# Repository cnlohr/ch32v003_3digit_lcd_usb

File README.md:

# ch32v003_3digit_lcd_usb

USB, Touch and Driver for 3-digit 7-segment TN LCDs on CH32V003

[Youtube Video](https://www.youtube.com/watch?v=KNDRUWlsu0k)

Using a ch32v003, a 10 cent microcontroller, without USB, Touch or LCD Driving capaibilities to do all three at the same time.

## Design

The design uses the reference rv003usb pinout, simply run the ch32v003 at 3.3v with an LDO and connect it up to the USB paddle card.

Conveniently the paddle card uses the same pinout as a normal USB Connector.

The overall board uses the inside part of a USB Type C connector, but as part of the PCB, so there are the following two recommendations:

1. Your PCB should be 0.6mm thick.
2. Your PCB sohuld use ENIG finish instead of HASL, as it is possible a HASL finish could damage USB-C cables.

The ch32v003 needs no preprogramming, only access to the GND/SWIO/5V pins to flash the bootloader on.

To use this design, your LCD must be a 3V LCD and should match the following specification:

## Software

To flash on the software, you should:

 * Optionally, install the rv003usb bootloader.

Then, from either external programmer or bootloader,

 * In your desired firmware folder type `make option_write`
 * Flash with `make flash`

Appropriate firmware can be found in the firmware/ folders.  When cloning this repo, be sure to clone recursively, i.e.

```
git clone https://github.com/cnlohr/ch32v003_3digit_lcd_usb --recursive
```

or if you, forgot, cd into the folder and run:
```
git submodule update --init --recursive
```

## Touch Sensing

To perform touch sensing, we drive the line low, then, in concert with starting the ADC sample (and making sure the ADC setup/sample is aligned in time to Fcpu/2) we apply a pull-up resistor to all the ports on the LCD.

This causes a measurement to be made as the voltage on the pins common to the whole LCD is rising and this gives us our measurement.

## Waveforms

For basic LCD output, you can use a fairly simple waveform that has 10 stages.

 * Stages 0..3 = Specific COM pins are driven LOW in succession, while any segments to light are turned HIGH.
 * Stage 4 = Free time, make sure there is no voltage differential.  This also helps control contrast.
 * Stage 5..8 = Specific COM pins are driven HIGH in succession, while any segments to light are turned LOW.
 * Stage 9 = The other half of the free time for contrast.

You can see how enabling USB wrecks things up, because with USB going, it can't regulate the SEG pins to 1/2 VCC.

For touch, the output is repeatedly released from a low voltage with an internal pullup while simultaneously measuring the voltage with an ADC to obtain the touch amount.

Which looks great until USB sails its boat into it.

## Resources

 * Applicaiton Note: [NXP AN3129](https://www.nxp.com/docs/en/application-note/AN3219.pdf)
 * [ch32v003fun](https://github.com/cnlohr/ch32v003fun)
 * [rv003usb](https://github.com/cnlohr/ch32v003fun)

Search Aliexpress for "TN LCD Segment" to find these little bad boys.

## License

All code and designs may by licensed freely under the MIT/x11 License.

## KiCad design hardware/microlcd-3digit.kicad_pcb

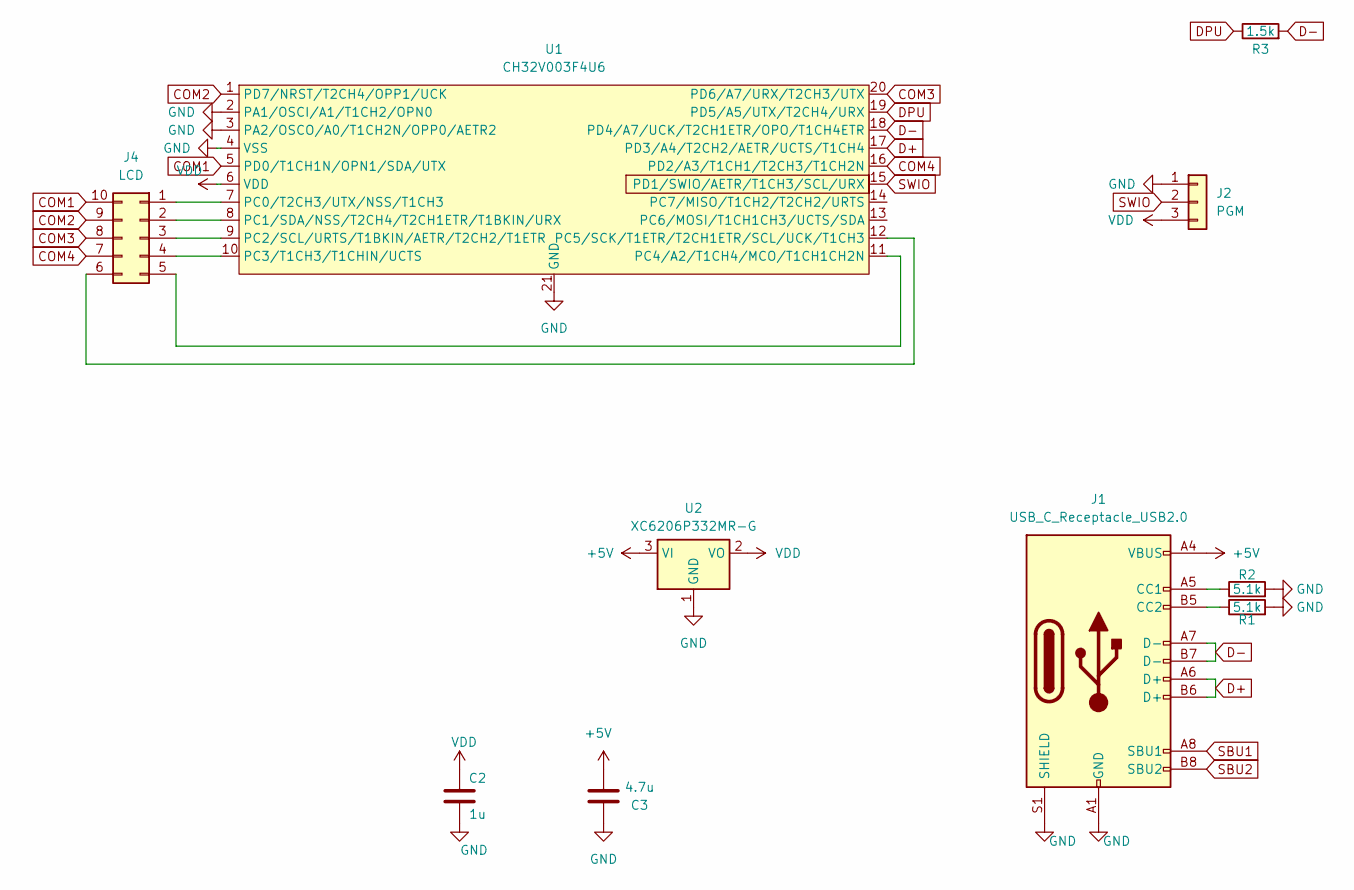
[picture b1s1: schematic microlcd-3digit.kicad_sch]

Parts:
C2: 1u; R_0402_1005Metric; LCSC C52923
C3: 4.7u; R_0402_1005Metric; LCSC C23733
J1: USB_C_Receptacle_USB2.0; USB_C_PADDLE
J2: PGM; PinHeader_1x03_P2.54mm_Vertical
J4: LCD; TINY_LCD_3_DIGIT
R1, R2: 5.1k; R_0402_1005Metric; LCSC C25905
R3: 1.5k; R_0402_1005Metric; LCSC C25867
U1: CH32V003F4U6; QFN-20-1EP_3x3mm_P0.4mm_EP1.65x1.65mm; LCSC C5299908
U2: XC6206P332MR-G; SOT-23; LCSC C5446

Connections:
+5V: C3.2, J1.A4 (VBUS), J1.A9 (VBUS), J1.B4 (VBUS), J1.B9 (VBUS), U2.3 (VI)
COM1: J4.7, U1.16 (PD2/A3/T1CH1/T2CH3/T1CH2N)
COM2: J4.8, U1.20 (PD6/A7/URX/T2CH3/UTX)
COM3: J4.9, U1.1 (PD7/NRST/T2CH4/OPP1/UCK)
COM4: J4.10, U1.5 (PD0/T1CH1N/OPN1/SDA/UTX)
D+: J1.A6 (D+), J1.B6 (D+), U1.17 (PD3/A4/T2CH2/AETR/UCTS/T1CH4)
D-: J1.A7 (D-), J1.B7 (D-), R3.2, U1.18 (PD4/A7/UCK/T2CH1ETR/OPO/T1CH4ETR)
DPU: R3.1, U1.19 (PD5/A5/UTX/T2CH4/URX)
GND: C2.1, C3.1, J1.A1 (GND), J1.A12 (GND), J1.B1 (GND), J1.B12 (GND), J1.S1 (SHIELD), J2.1, R1.2, R2.2, U1.2 (PA1/OSCI/A1/T1CH2/OPN0), U1.3 (PA2/OSCO/A0/T1CH2N/OPP0/AETR2), U1.4 (VSS), U1.21 (GND), U2.1 (GND)
unnamed: J1.A5 (CC1), R2.1
unnamed: J1.B5 (CC2), R1.1
unnamed: J4.1, U1.7 (PC0/T2CH3/UTX/NSS/T1CH3)
unnamed: J4.2, U1.8 (PC1/SDA/NSS/T2CH4/T2CH1ETR/T1BKIN/URX)
unnamed: J4.3, U1.9 (PC2/SCL/URTS/T1BKIN/AETR/T2CH2/T1ETR)
unnamed: J4.4, U1.10 (PC3/T1CH3/T1CHIN/UCTS)
unnamed: J4.5, U1.11 (PC4/A2/T1CH4/MCO/T1CH1CH2N)
unnamed: J4.6, U1.12 (PC5/SCK/T1ETR/T2CH1ETR/SCL/UCK/T1CH3)
SBU1: J1.A8 (SBU1)
SBU2: J1.B8 (SBU2)
SWIO: J2.2, U1.15 (PD1/SWIO/AETR/T1CH3/SCL/URX)
VDD: C2.2, J2.3, U1.6 (VDD), U2.2 (VO)

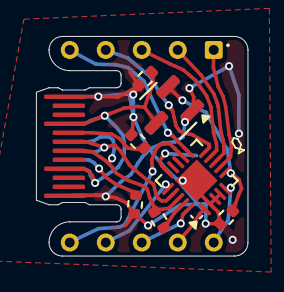
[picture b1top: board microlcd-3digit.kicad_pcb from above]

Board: 2 copper layers, 11.8 x 12.2 mm, 10 parts (1 on the bottom side), 19 nets.

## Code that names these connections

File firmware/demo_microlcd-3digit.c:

#include "ch32v003fun.h"
#include <stdio.h>
#include <string.h>
#include "rv003usb.h"

// Allow reading and writing to the scratchpad via HID control messages.
uint8_t scratch[63];
volatile uint8_t start_leds = 0;
uint8_t ledat;

#define LCDCOM1 PD0
#define LCDCOM2 PD7
#define LCDCOM3 PD6
#define LCDCOM4 PD2

#define LCDSEGBUF GPIOC

#define LEDSEG0 PC0
#define LEDSEG1 PC1
#define LEDSEG2 PC2
#define LEDSEG3 PC3
#define LEDSEG4 PC4
#define LEDSEG5 PC5

// from host
static uint32_t lastmask;


static uint8_t frame;

// LCD Is 10PIN TN Positive 3-Digits 7 Segment LCD Panel 3.0V

//  bbb
//  a d
//  ccc
//  e f
//  ggg
// ab0000cd0000ef0000g0

const uint32_t digits[16] = {
	0b11000001000011000010, // 0
	0b00000001000001000000, // 1
	0b01000011000010000010, // 2
	0b01000011000001000010, // 3
	0b10000011000001000000, // 4
	0b11000010000001000010, // 5
	0b11000010000011000010, // 6
	0b11000001000001000000, // 7
	0b11000011000011000010, // 8
	0b11000011000001000010, // 9
	0b11000011000011000000, // A
	0b10000010000011000010, // b
	0b00000010000010000010, // c
	0b00000011000011000010, // d
	0b11000010000010000010, // e
	0b11000010000010000000, // f
};

uint32_t ComputeLCDMaskWithNumber( uint32_t val )
{
	int i;
	uint32_t mask = 0;
	for( i = 0; i < 3; i++ )
	{
		uint32_t vv = (val >> 8);
		mask <<= 2;
		if( vv > 0 || i == 2 )
		{
			mask |= digits[vv & 0xf];
		}
		val <<= 4;
	}
	return mask;
}

void UpdateLCD( uint32_t mask )
{
	int group;
	uint8_t pinset[4] = { LCDCOM1, LCDCOM2, LCDCOM3, LCDCOM4 };

	#define drivepr GPIO_CFGLR_IN_PUPD

	for( group = 0; group < 4; group++ )
		funPinMode( pinset[group], drivepr );

	funPinMode( LEDSEG0, drivepr );
	funPinMode( LEDSEG1, drivepr );
	funPinMode( LEDSEG2, drivepr );
	funPinMode( LEDSEG3, drivepr );
	funPinMode( LEDSEG4, drivepr );
	funPinMode( LEDSEG5, drivepr );

	for( group = 0; group < 4; group++ )
	{
		LCDSEGBUF->BSHR = mask&0x3f;
		funDigitalWrite( pinset[group], 0 );
		Delay_Us(300);
		LCDSEGBUF->BSHR = 0x3f<<16;
		funDigitalWrite( pinset[group], 1 );
		Delay_Us(10);
		mask>>=6;
	}

	Delay_Us(3000);
}

int main()
{
	SystemInit();
	Delay_Ms(3); // Ensures USB re-enumeration after bootloader or reset; Spec demand >2.5µs ( TDDIS )
	usb_setup();

	funGpioInitAll();

	int id = 0;
	int didaffect = 0;
	while(1)
	{
		if( !didaffect )
		{
			id++;
			UpdateLCD( ComputeLCDMaskWithNumber( id >> 4 ) );
		}
		else
		{
			UpdateLCD( lastmask );
		}
		//printf( "%lu %lu %lu %08lx\n", rv003usb_internal_data.delta_se0_cyccount, rv003usb_internal_data.last_se0_cyccount, rv003usb_internal_data.se0_windup, RCC->CTLR );
#if RV003USB_EVENT_DEBUGGING
		uint32_t * ue = GetUEvent();
		if( ue )
		{
			printf( "%lu %lx %lx %lx\n", ue[0], ue[1], ue[2], ue[3] );
		}
#endif
		if( start_leds )
		{
			memcpy( &lastmask, scratch+1, 4 );
			didaffect = 1;
			start_leds = 0;
			frame++;
		}
	}
}

void usb_handle_user_in_request( struct usb_endpoint * e, uint8_t * scratchpad, int endp, uint32_t sendtok, struct rv003usb_internal * ist )
{
	// Make sure we only deal with control messages.  Like get/set feature reports.
	if( endp )
	{
		usb_send_empty( sendtok );
	}
}

void usb_handle_user_data( struct usb_endpoint * e, int current_endpoint, uint8_t * data, int len, struct rv003usb_internal * ist )
{
	//LogUEvent( SysTick->CNT, current_endpoint, e->count, 0xaaaaaaaa );
	int offset = e->count<<3;
	int torx = e->max_len - offset;
	if( torx > len ) torx = len;
	if( torx > 0 )
	{
		memcpy( scratch + offset, data, torx );
		e->count++;
		if( ( e->count << 3 ) >= e->max_len )
		{
			start_leds = e->max_len;
		}
	}
}

void usb_handle_hid_get_report_start( struct usb_endpoint * e, int reqLen, uint32_t lValueLSBIndexMSB )
{
	if( reqLen > sizeof( scratch ) ) reqLen = sizeof( scratch );

	// You can check the lValueLSBIndexMSB word to decide what you want to do here
	// But, whatever you point this at will be returned back to the host PC where
	// it calls hid_get_feature_report. 
	//
	// Please note, that on some systems, for this to work, your return length must
	// match the length defined in HID_REPORT_COUNT, in your HID report, in usb_config.h

	e->opaque = scratch;
	e->max_len = reqLen;
}

void usb_handle_hid_set_report_start( struct usb_endpoint * e, int reqLen, uint32_t lValueLSBIndexMSB )
{
	// Here is where you get an alert when the host PC calls hid_send_feature_report.
	//
	// You can handle the appropriate message here.  Please note that in this
	// example, the data is chunked into groups-of-8-bytes.
	//
	// Note that you may need to make this match HID_REPORT_COUNT, in your HID
	// report, in usb_config.h

	if( reqLen > sizeof( scratch ) ) reqLen = sizeof( scratch );
	e->max_len = reqLen;
}


void usb_handle_other_control_message( struct usb_endpoint * e, struct usb_urb * s, struct rv003usb_internal * ist )
{
	LogUEvent( SysTick->CNT, s->wRequestTypeLSBRequestMSB, s->lValueLSBIndexMSB, s->wLength );
}

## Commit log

2024-11-22 Giving a shot at touch
2024-11-23 Found some magic settings.
2024-11-23 touch pad with counter
2024-11-23 Getting closer but still not right
2024-11-25 Update touch + rv003usb + docs
2024-11-25 Swap things around to use dither control for generating 1/2 VCC
2024-11-26 Fix dithering
2024-11-26 Add waveform info
2024-11-26 Update with some more waveforms
2024-11-26 Fixup touch code to be perfect.
2024-12-01 Add application note
2024-12-04 Add keyboard-only-f-button
2024-12-16 Update content
2024-12-16 Add TN note
